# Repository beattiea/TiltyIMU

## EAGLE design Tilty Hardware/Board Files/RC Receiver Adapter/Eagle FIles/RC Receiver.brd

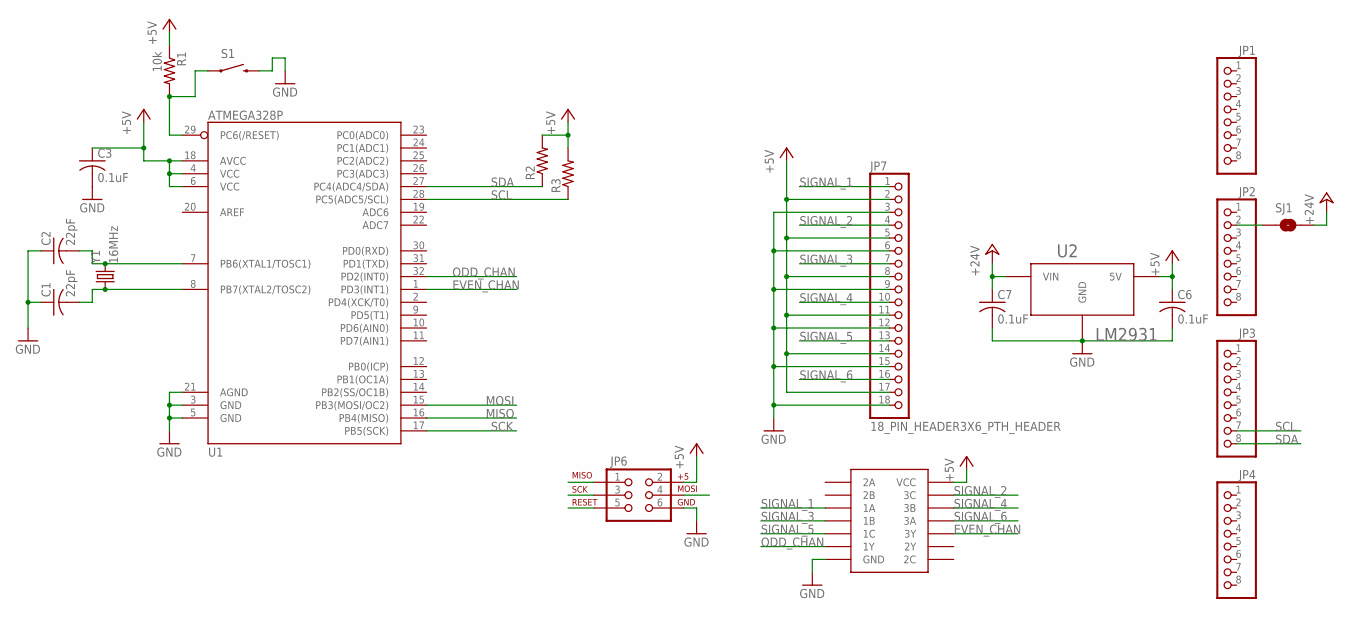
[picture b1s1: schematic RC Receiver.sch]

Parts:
C1, C2: 22pF; C0603
C3, C6, C7: 0.1uF; C0603
JP1, JP2, JP3, JP4: PINHD-1X81X08_NO_SILK; 1X08_NO_SS
JP6: AVR_SPI_PRG_62X3_LOCK; 2X3_LOCK
JP7: 18_PIN_HEADER3X6_PTH_HEADER; 3X6_PTH_HEADER
R1: 10k; R0603
R2, R3: R-US_R0603; R0603
S1: SWITCH-MOMENTARY-2SMD; TACTILE_SWITCH_SMD
SJ1: SOLDERJUMPERNC; SJ_2S
U1: ATMEGA328P; TQFP32-08
U2: LM2931; TO263; PART# lm2931
U$1: C74HC407514-SOIC; 14-SOIC; PART# 296-14534-1-ND
Y1: 16MHz; CRYSTAL-SMD-5X3; PART# 535-10226-1-ND

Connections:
+5V: C3.1, C6.1, JP6.2, JP7.2, JP7.5, JP7.8, JP7.11, JP7.14, JP7.17, R1.1, R2.2, R3.2, U1.4 (VCC), U1.6 (VCC), U1.18 (AVCC), U2.P$3 (5V), U$1.P$14 (VCC)
+24V: C7.1, SJ1.2, U2.P$2 (VIN)
EVEN_CHAN: U1.1 (PD3(INT1)), U$1.P$12 (3Y)
GND: C1.1, C2.1, C3.2, C6.2, C7.2, JP6.6, JP7.3, JP7.6, JP7.9, JP7.12, JP7.15, JP7.18, S1.3 (2), U1.3 (GND), U1.5 (GND), U1.21 (AGND), U2.P$1 (GND), U$1.P$13 (GND)
MISO: JP6.1, U1.16 (PB4(MISO))
MOSI: JP6.4, U1.15 (PB3(MOSI/OC2))
unnamed: C2.2, U1.7 (PB6(XTAL1/TOSC1)), Y1.3 (2)
unnamed: C1.2, U1.8 (PB7(XTAL2/TOSC2)), Y1.1
unnamed: JP2.2, SJ1.1
ODD_CHAN: U1.32 (PD2(INT0)), U$1.P$4 (1Y)
RESET: JP6.5, R1.2, S1.1, U1.29 (PC6(/RESET))
SCK: JP6.3, U1.17 (PB5(SCK))
SCL: JP3.7, R3.1, U1.28 (PC5(ADC5/SCL))
SDA: JP3.8, R2.1, U1.27 (PC4(ADC4/SDA))
SIGNAL_1: JP7.1, U$1.P$1 (1A)
SIGNAL_2: JP7.4, U$1.P$11 (3C)
SIGNAL_3: JP7.7, U$1.P$2 (1B)
SIGNAL_4: JP7.10, U$1.P$10 (3B)
SIGNAL_5: JP7.13, U$1.P$3 (1C)
SIGNAL_6: JP7.16, U$1.P$9 (3A)

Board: 2 copper layers, 20 parts (0 on the bottom side), 20 nets, no tracks yet.

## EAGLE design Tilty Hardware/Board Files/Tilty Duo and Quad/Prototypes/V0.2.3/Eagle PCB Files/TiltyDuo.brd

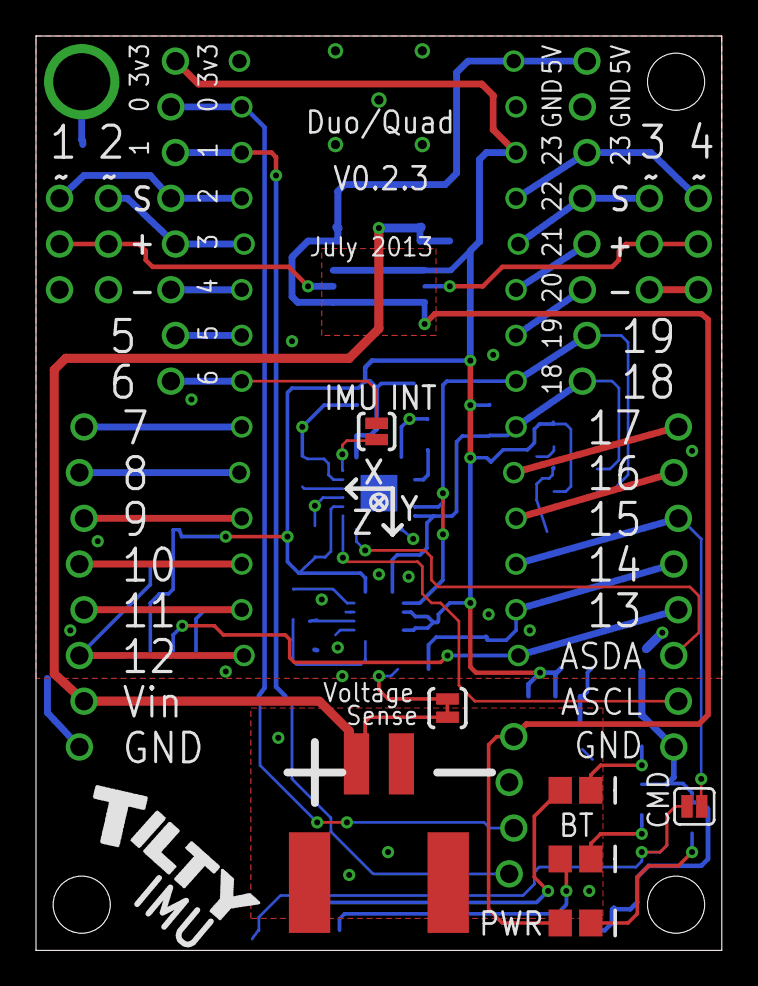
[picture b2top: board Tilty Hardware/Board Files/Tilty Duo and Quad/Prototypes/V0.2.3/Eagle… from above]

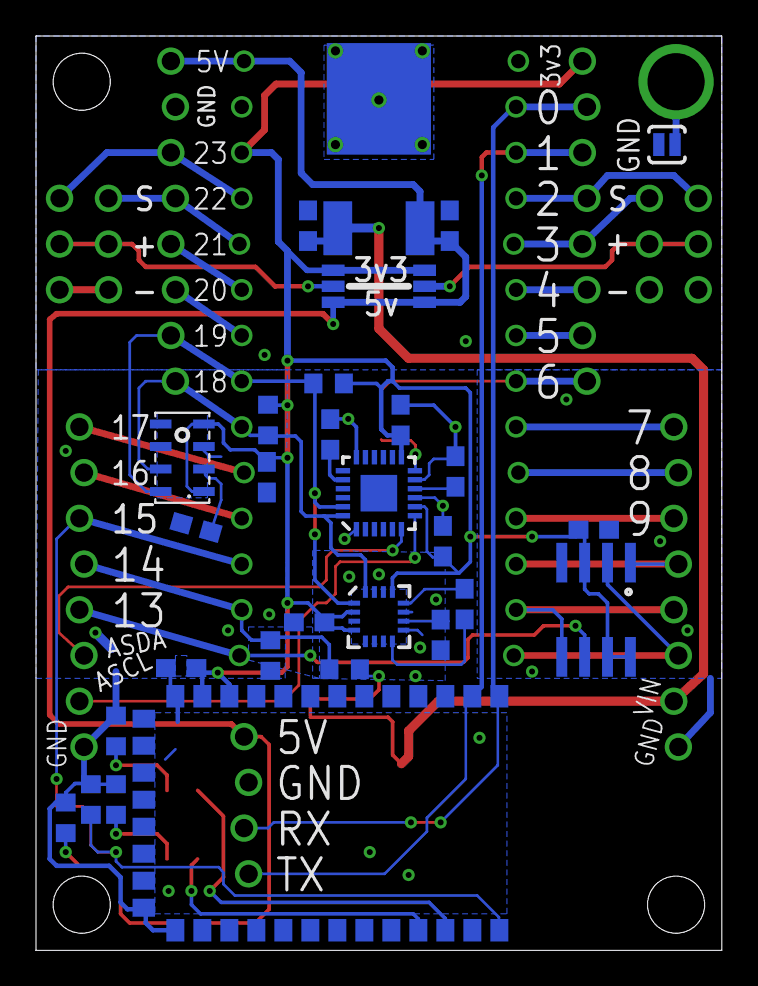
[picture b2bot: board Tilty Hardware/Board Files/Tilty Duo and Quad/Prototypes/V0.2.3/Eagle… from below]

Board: 2 copper layers, 38.1 x 50.8 mm, 45 parts (30 on the bottom side), 46 nets.

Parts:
C1, C2, C4, C5, C6, C9, C10, C11, C12, C13: 0.1uF; C0603
C3: 2.2nF; C0603
C7: 0.22uF; C0603
C8: 4.7uF; C0603
D1: RED; LED-0805
D2: GREEN; LED-0805
D3: YELLOW; LED-0805
JP1, JP2, JP5, JP6: 1X08_NO_SS_LOCKING
JP3, JP7: 2X03_NO_SS_LOCK
JP4: 2-POS_SMD_TERM_BLOCK; 2-POS_SMD_TERMINAL_BLOCK
JP9: 1X04_NO_SS_LOCKING
MPU_INT: SOLDERJUMPERNO; SJ_2S-NO
R1, R2: 4.7K; R0603
R3: 180; R0603
R4, R8: 68; R0603
R5: 10k; R0603
R6: 680; R0603
R7: 10K; R0603
SJ1: SOLDERJUMPERNO; SJ_2S-NO
SJ2, SJ3: SJ_3
SJ4: SOLDERJUMPERTRACE; SJ_2S-TRACE
SJ5: SJ_2S
U1: TEENSY_3.0_OUTER-PINS28-DIP_SOCKET; 28-DIP
U2: HC-09_BREAKOUT
U3: MPL3115A2LGA8; LGA8
U4: LM2931; TO263
U5: MPU-6050; QFN-24
U6: HMC5883LSMD; 16LPCC
U7: SPI_FLASH-X25XXSMD; SO08

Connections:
5V: C5.1, D2.1, JP5.8, JP9.4, SJ2.1, SJ3.1, U1.P$15, U4.P$3
AUXCL: JP6.2, U5.7
AUXDA: JP6.3, U5.6
BATT_SENSE: JP6.5, R5.2, R6.2, U1.P$27
BT_CMD: JP6.6, SJ5.1, U1.P$26
CMD: R7.2, SJ5.2, U2.P$34
CS: JP2.5, U1.P$12, U7.1
GND: C1.2, C2.1, C3.2, C4.2, C5.2, C6.2, C8.2, C9.2, C10.2, C11.1, C12.1, C13.1, JP2.1, JP3.1, JP3.2, JP4.P$4, JP5.7, JP6.1, JP7.1, JP7.2, JP9.3, R3.1, R4.2, R6.1, R7.1, R8.1, SJ1.2, U1.P$1, U1.P$16, U2.P$13, U2.P$21, U2.P$22, U3.3, U4.P$1, U5.1, U5.9, U5.11, U5.18, U6.9, U6.11, U7.4
I/O1: JP1.5, JP3.6, U1.P$4
I/O2: JP1.4, JP3.5, U1.P$5
I/O3: JP5.6, JP7.5, U1.P$18
I/O4: JP5.5, JP7.6, U1.P$19
MISO: JP2.3, U1.P$14, U7.2
MOSI: JP2.4, U1.P$13, U7.5
MPU_INT: JP1.1, MPU_INT.1, U1.P$8
unnamed: C1.1, U5.10
unnamed: C3.1, U5.20
unnamed: D1.2, R3.2
unnamed: C7.1, U6.8
unnamed: C7.2, U6.12
unnamed: JP1.3, U1.P$6
unnamed: JP1.2, U1.P$7
unnamed: R5.1, SJ4.2
unnamed: JP6.8, U1.P$24
unnamed: C8.1, U6.10
unnamed: JP2.6, U1.P$11
unnamed: D2.2, R4.1
unnamed: MPU_INT.2, U5.12
unnamed: JP5.4, U1.P$20
unnamed: JP5.3, U1.P$21
unnamed: C10.1, U3.2
unnamed: JP6.7, U1.P$25
unnamed: D3.2, R8.2
POW_I/O1: JP3.3, JP3.4, SJ2.2
POW_I/O2: JP7.3, JP7.4, SJ3.2
RED_LED: D1.1, U2.P$32
RX1: JP1.7, JP9.2, U1.P$2, U2.P$1
RX3: JP2.8, U1.P$9
SCK: JP6.4, U1.P$28, U7.6
SCL: JP5.2, R1.1, U1.P$22, U3.8, U5.23, U6.1
SDA: JP5.1, R2.1, U1.P$23, U3.7, U5.24, U6.16
TEENSY_3V3: C2.2, C6.1, C9.1, C11.2, C12.2, C13.2, JP1.8, R1.2, R2.2, SJ2.3, SJ3.3, U1.P$17, U2.P$11, U2.P$12, U3.1, U3.4, U5.8, U5.13, U6.2, U6.4, U6.13, U7.3, U7.7, U7.8
TX1: JP1.6, JP9.1, U1.P$3, U2.P$2
TX3: JP2.7, U1.P$10
VBATT: C4.1, JP2.2, JP4.P$3, SJ4.1, U4.P$2
YEL_LED: D3.1, U2.P$31

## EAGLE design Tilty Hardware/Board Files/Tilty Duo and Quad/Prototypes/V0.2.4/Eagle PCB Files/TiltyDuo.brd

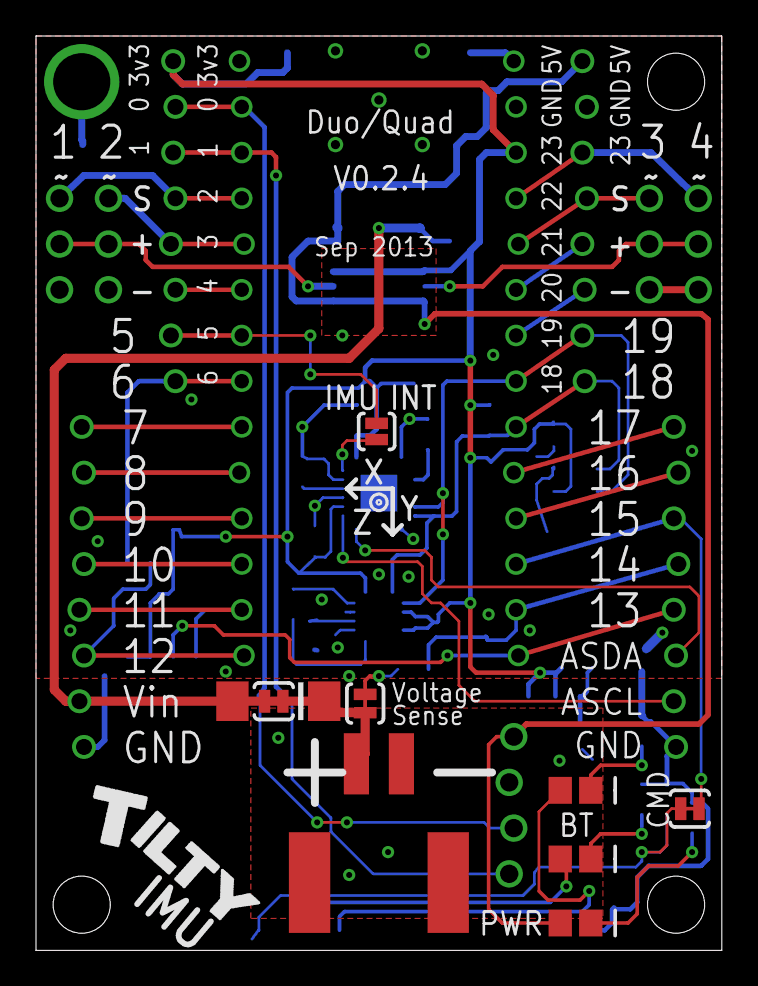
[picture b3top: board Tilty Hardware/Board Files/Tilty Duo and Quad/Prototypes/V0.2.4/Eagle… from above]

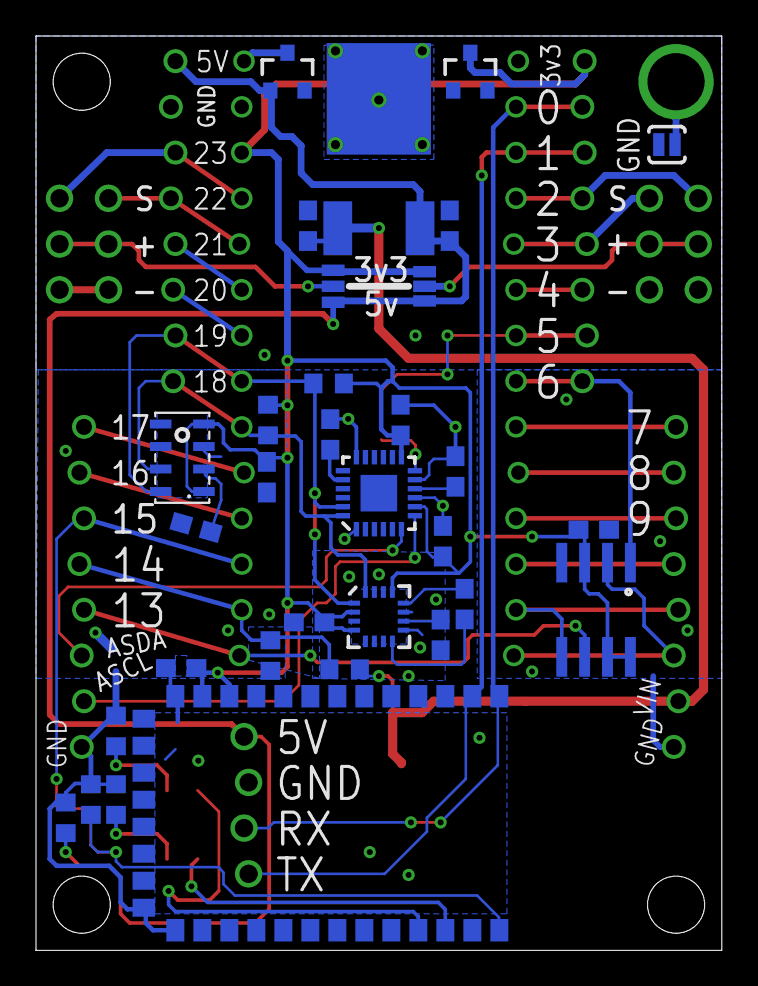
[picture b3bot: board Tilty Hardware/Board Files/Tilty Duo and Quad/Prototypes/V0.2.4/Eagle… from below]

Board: 2 copper layers, 38.1 x 50.8 mm, 49 parts (32 on the bottom side), 47 nets.

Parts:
C1, C2, C4, C6, C9, C10, C11, C12, C13: 0.1uF; C0603
C3: 2.2nF; C0603
C5, C8: 4.7uF; C0603
C7: 0.22uF; C0603
D1: RED; LED-0805
D2: GREEN; LED-0805
D3: YELLOW; LED-0805
D4, D5: SOT23-3
D6: DO214AA
JP1, JP2, JP3, JP4: 8-PIN_HEADER; 8-PIN_RECEPTACLE_LOCK_NO-SS
JP5: 2-POS_SMD_TERM_BLOCK; 2-POS_SMD_TERMINAL_BLOCK
JP6, JP7: 2X03_NO_SS_LOCK
JP9: 1X04_NO_SS_LOCKING
MPU_INT: SOLDERJUMPERNO; SJ_2S-NO
R1, R2: 4.7K; R0603
R3: 180; R0603
R4, R8: 68; R0603
R5: 10k; R0603
R6: 680; R0603
R7: 10K; R0603
SJ1: SOLDERJUMPERNO; SJ_2S-NO
SJ2: SJ_3_PASTE1&2
SJ3: SJ_3
SJ4, SJ5, SJ6: SOLDERJUMPERTRACE; SJ_2S-TRACE
U1: TEENSY_3.0_OUTER-PINS28-DIP_SOCKET; 28-DIP
U2: HC-09_BREAKOUT
U3: MPL3115A2LGA8; LGA8
U4: LM2931; TO263
U5: MPU-6050; QFN-24
U6: HMC5883LSMD; 16LPCC
U7: SPI_FLASH-X25XXSMD; SO08

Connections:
5V: C5.1, D2.1, D4.1, JP4.P$1, JP9.4, SJ2.1, SJ3.1, U4.P$3
AUXCL: JP3.P$7, U5.7
AUXDA: JP3.P$6, U5.6
BATT_SENSE: JP3.P$4, R5.2, R6.2, U1.P$27
BT_CMD: JP3.P$3, SJ5.1, U1.P$26
CMD: R7.2, SJ5.2, U2.P$34
CS: JP1.P$1, U1.P$8, U7.1
GND: C1.2, C2.1, C3.2, C4.2, C5.2, C6.2, C8.2, C9.2, C10.2, C11.1, C12.1, C13.1, D5.1, JP2.P$1, JP3.P$8, JP4.P$2, JP5.P$4, JP6.1, JP6.2, JP7.1, JP7.2, JP9.3, R3.1, R4.2, R6.1, R7.1, R8.1, SJ1.2, U1.P$1, U1.P$16, U2.P$13, U2.P$21, U2.P$22, U3.3, U4.P$1, U5.1, U5.9, U5.11, U5.18, U6.9, U6.11, U7.4
I/O1: JP1.P$5, JP6.6, U1.P$4
I/O2: JP1.P$4, JP6.5, U1.P$5
I/O3: JP4.P$3, JP7.5, U1.P$18
I/O4: JP4.P$4, JP7.6, U1.P$19
MISO: JP2.P$3, U1.P$14, U7.2
MOSI: JP2.P$4, U1.P$13, U7.5
MPU_INT: JP1.P$2, MPU_INT.1, U1.P$7
unnamed: C1.1, U5.10
unnamed: C3.1, U5.20
unnamed: D1.2, R3.2
unnamed: C7.1, U6.8
unnamed: C7.2, U6.12
unnamed: JP1.P$3, U1.P$6
unnamed: JP2.P$5, U1.P$12
unnamed: R5.1, SJ4.2
unnamed: JP3.P$1, U1.P$24
unnamed: C8.1, U6.10
unnamed: JP2.P$6, U1.P$11
unnamed: D2.2, R4.1
unnamed: D1.1, U2.P$31
unnamed: D4.3, U1.P$15
unnamed: MPU_INT.2, U5.12
unnamed: JP4.P$5, U1.P$20
unnamed: JP4.P$6, U1.P$21
unnamed: C10.1, U3.2
unnamed: JP3.P$2, U1.P$25
unnamed: D3.2, R8.2
POW_I/O1: JP6.3, JP6.4, SJ2.2
POW_I/O2: JP7.3, JP7.4, SJ3.2
RX1: JP1.P$7, JP9.2, U1.P$2, U2.P$1
RX3: JP2.P$8, U1.P$9
SCK: JP3.P$5, U1.P$28, U7.6
SCL: JP4.P$7, R1.1, U1.P$22, U3.8, U5.23, U6.1
SDA: JP4.P$8, R2.1, U1.P$23, U3.7, U5.24, U6.16
TEENSY_3V3: C2.2, C6.1, C9.1, C11.2, C12.2, C13.2, D5.3, JP1.P$8, R1.2, R2.2, SJ2.3, SJ3.3, U1.P$17, U2.P$11, U2.P$12, U3.1, U3.4, U5.8, U5.13, U6.2, U6.4, U6.13, U7.3, U7.7, U7.8
TX1: JP1.P$6, JP9.1, U1.P$3, U2.P$2
TX3: JP2.P$7, U1.P$10
VBATT: C4.1, D6.A, D6.C, JP2.P$2, JP5.P$3, SJ4.1, SJ6.1, SJ6.2, U4.P$2
YEL_LED: D3.1, U2.P$32

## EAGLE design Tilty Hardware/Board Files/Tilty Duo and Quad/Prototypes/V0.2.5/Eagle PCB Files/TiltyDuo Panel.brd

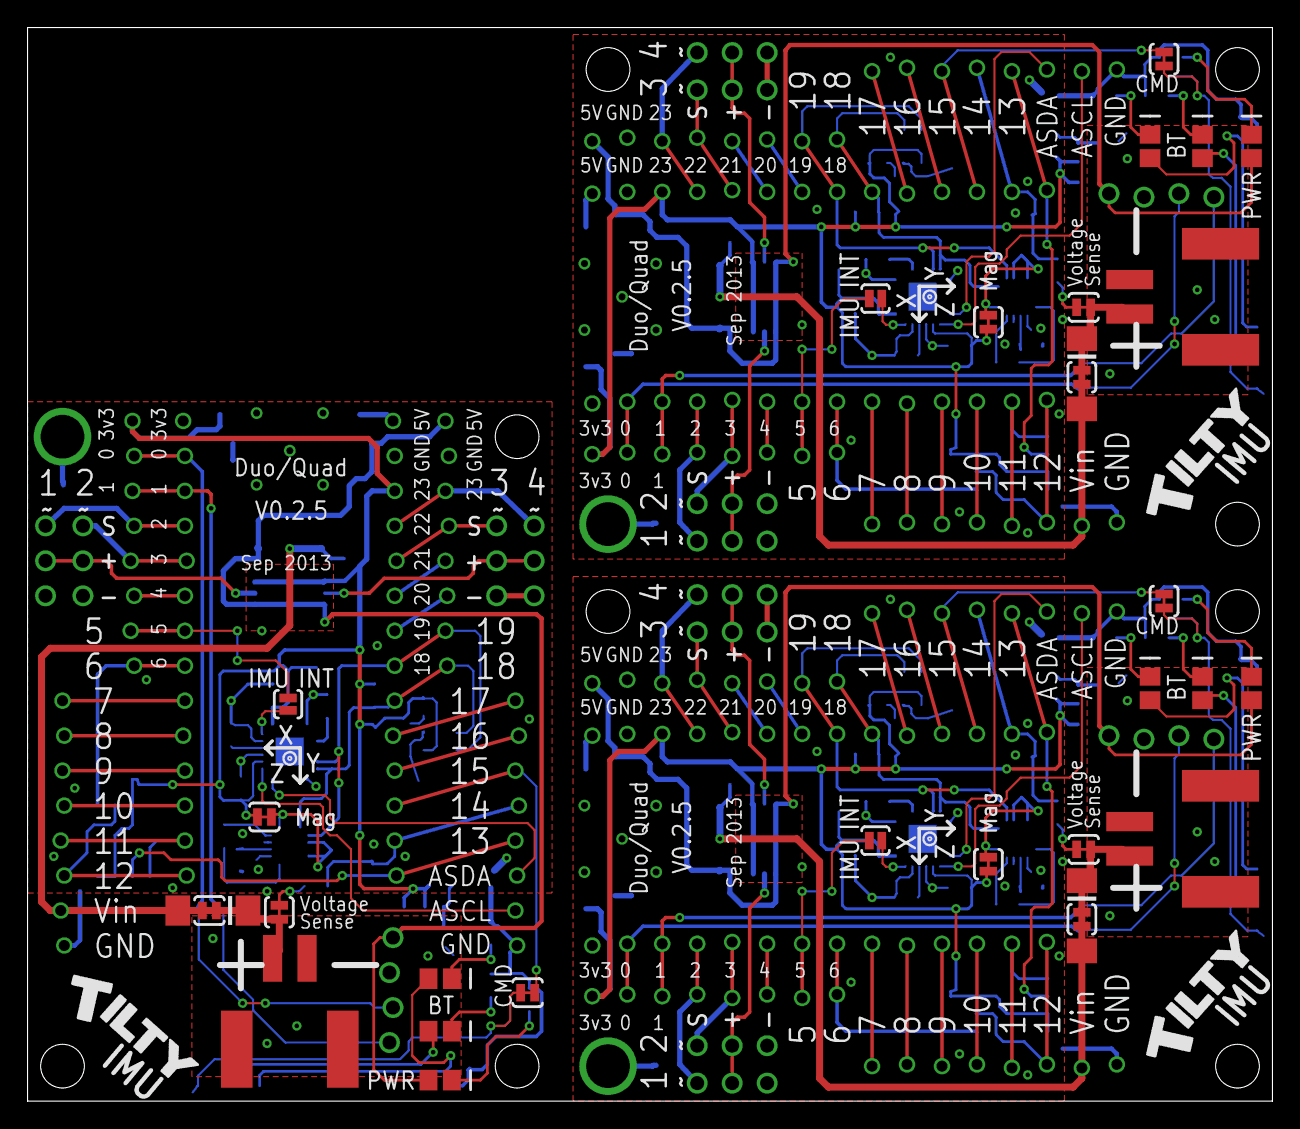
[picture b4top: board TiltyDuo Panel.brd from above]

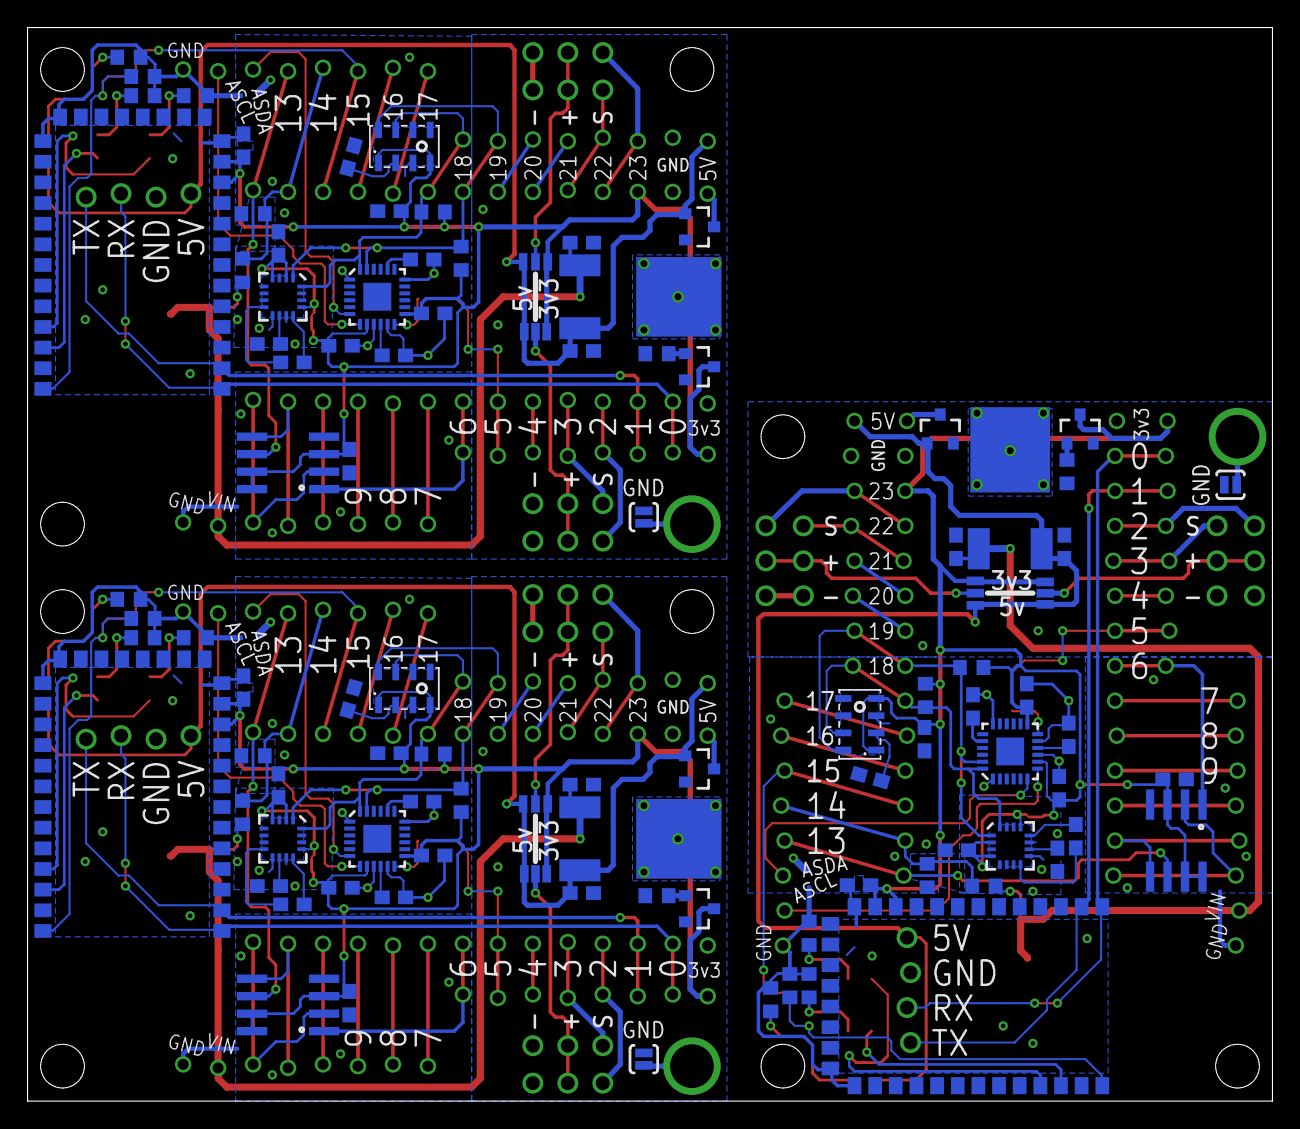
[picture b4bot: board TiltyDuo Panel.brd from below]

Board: 2 copper layers, 90.4 x 78.0 mm, 153 parts (99 on the bottom side), 147 nets.

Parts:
C1, C2, C4, C6, C9, C10, C11, C12, C13, C14, C15, C17, C21, C22, C23, C24, C25, C26, C27, C28, C30, C34, C35, C36, C37, C38, C39: 0.1uF; C0603
C3, C16, C29: 2.2nF; C0603
C5, C8, C18, C20, C31, C33: 4.7uF; C0603
C7, C19, C32: 0.22uF; C0603
D1, D7, D13: RED; LED-0805
D2, D8, D14: GREEN; LED-0805
D3, D9, D15: YELLOW; LED-0805
D4, D5, D10, D11, D16, D17: SOT23-3
D6, D12, D18: DO214AA
JP1, JP2, JP3, JP4, JP13, JP14, JP15, JP16, JP21, JP22, JP23, JP24: 8-PIN_HEADER; 8-PIN_RECEPTACLE_LOCK_NO-SS
JP5, JP8, JP17: 2-POS_SMD_TERM_BLOCK; 2-POS_SMD_TERMINAL_BLOCK
JP6, JP7, JP10, JP11, JP18, JP19: 2X03_NO_SS_LOCK
JP9, JP12, JP20: 1X04_NO_SS_LOCKING
MPU_INT, MPU_INT1, MPU_INT2: SOLDERJUMPERNO; SJ_2S-NO
R1, R2, R10, R11, R19, R20: 4.7K; R0603
R3, R15, R24: 180; R0603
R4, R8, R16, R17, R25, R26: 68; R0603
R5, R12, R21: 10k; R0603
R6, R13, R22: 680; R0603
R7, R14, R23: 10K; R0603
R9, R18, R27: R0603
SJ1, SJ8, SJ15: SOLDERJUMPERNO; SJ_2S-NO
SJ2, SJ10, SJ17: SJ_3_PASTE1&2
SJ3, SJ9, SJ16: SJ_3
SJ4, SJ5, SJ6, SJ7, SJ11, SJ12, SJ13, SJ14, SJ18, SJ19, SJ20, SJ21: SOLDERJUMPERTRACE; SJ_2S-TRACE
U1, U11, U18: TEENSY_3.0_OUTER-PINS28-DIP_SOCKET; 28-DIP
U2, U9, U16: HC-09_BREAKOUT
U3, U13, U20: MPL3115A2LGA8; LGA8
U4, U10, U17: LM2931; TO263
U5, U8, U15: MPU-6050; QFN-24
U6, U12, U19: HMC5883LSMD; 16LPCC
U7, U14, U21: SPI_FLASH-X25XXSMD; SO08

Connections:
5V: C5.1, D2.1, D4.1, JP4.P$1, JP9.4, SJ2.1, SJ3.1, U4.P$3
5V1: C18.1, D8.1, D10.1, JP12.4, JP13.P$1, SJ9.1, SJ10.1, U10.P$3
5V2: C31.1, D14.1, D16.1, JP20.4, JP21.P$1, SJ16.1, SJ17.1, U17.P$3
AUXCL: JP3.P$7, U5.7
AUXCL1: JP14.P$7, U8.7
AUXCL2: JP22.P$7, U15.7
AUXDA: JP3.P$6, U5.6
AUXDA1: JP14.P$6, U8.6
AUXDA2: JP22.P$6, U15.6
BATT_SENSE: JP3.P$4, R5.2, R6.2, U1.P$27
BATT_SENSE1: JP14.P$4, R12.2, R13.2, U11.P$27
BATT_SENSE2: JP22.P$4, R21.2, R22.2, U18.P$27
BT_CMD: JP3.P$3, SJ5.1, U1.P$26
BT_CMD1: JP14.P$3, SJ13.1, U11.P$26
BT_CMD2: JP22.P$3, SJ20.1, U18.P$26
CMD: R7.2, SJ5.2, U2.P$34
CMD1: R14.2, SJ13.2, U9.P$34
CMD2: R23.2, SJ20.2, U16.P$34
CS: JP1.P$1, U1.P$8, U7.1
CS1: JP16.P$1, U11.P$8, U14.1
CS2: JP24.P$1, U18.P$8, U21.1
GND: C1.2, C2.1, C3.2, C4.2, C5.2, C6.2, C8.2, C9.2, C10.2, C11.1, C12.1, C13.1, JP2.P$1, JP3.P$8, JP4.P$2, JP5.P$4, JP6.1, JP6.2, JP7.1, JP7.2, JP9.3, R3.1, R4.2, R6.1, R7.1, R8.1, R9.1, SJ1.2, U1.P$1, U1.P$16, U2.P$13, U2.P$21, U2.P$22, U3.3, U4.P$1, U5.1, U5.9, U5.11, U5.18, U6.9, U6.11, U7.4
GND1: C14.2, C15.1, C16.2, C17.2, C18.2, C20.2, C21.2, C22.2, C23.2, C24.1, C25.1, C26.1, JP8.P$4, JP10.1, JP10.2, JP11.1, JP11.2, JP12.3, JP13.P$2, JP14.P$8, JP15.P$1, R13.1, R14.1, R15.1, R16.1, R17.2, R18.1, SJ8.2, U8.1, U8.9, U8.11, U8.18, U9.P$13, U9.P$21, U9.P$22, U10.P$1, U11.P$1, U11.P$16, U12.9, U12.11, U13.3, U14.4
GND2: C27.2, C28.1, C29.2, C30.2, C31.2, C33.2, C34.2, C35.2, C36.2, C37.1, C38.1, C39.1, JP17.P$4, JP18.1, JP18.2, JP19.1, JP19.2, JP20.3, JP21.P$2, JP22.P$8, JP23.P$1, R22.1, R23.1, R24.1, R25.1, R26.2, R27.1, SJ15.2, U15.1, U15.9, U15.11, U15.18, U16.P$13, U16.P$21, U16.P$22, U17.P$1, U18.P$1, U18.P$16, U19.9, U19.11, U20.3, U21.4
I/O1: JP1.P$5, JP6.6, U1.P$4
I/O2: JP1.P$4, JP6.5, U1.P$5
I/O3: JP4.P$3, JP7.5, U1.P$18
I/O4: JP4.P$4, JP7.6, U1.P$19
I/O5: JP10.6, JP16.P$5, U11.P$4
I/O6: JP10.5, JP16.P$4, U11.P$5
I/O7: JP11.6, JP13.P$4, U11.P$19
I/O8: JP11.5, JP13.P$3, U11.P$18
I/O9: JP18.6, JP24.P$5, U18.P$4
I/O10: JP18.5, JP24.P$4, U18.P$5
I/O11: JP19.6, JP21.P$4, U18.P$19
I/O12: JP19.5, JP21.P$3, U18.P$18
MISO: JP2.P$3, U1.P$14, U7.2
MISO1: JP15.P$3, U11.P$14, U14.2
MISO2: JP23.P$3, U18.P$14, U21.2
MOSI: JP2.P$4, U1.P$13, U7.5
MOSI1: JP15.P$4, U11.P$13, U14.5
MOSI2: JP23.P$4, U18.P$13, U21.5
MPU_INT: JP1.P$2, MPU_INT.1, U1.P$7
MPU_INT1: JP16.P$2, MPU_INT1.1, U11.P$7
MPU_INT2: JP24.P$2, MPU_INT2.1, U18.P$7
unnamed: C1.1, U5.10
unnamed: C3.1, U5.20
unnamed: D1.2, R3.2
unnamed: C7.1, U6.8
unnamed: C7.2, U6.12
unnamed: JP1.P$3, U1.P$6
unnamed: JP2.P$5, U1.P$12
unnamed: R5.1, SJ4.2
unnamed: JP3.P$1, U1.P$24
unnamed: C8.1, U6.10
unnamed: JP2.P$6, U1.P$11
unnamed: D2.2, R4.1
unnamed: D1.1, U2.P$31
unnamed: D4.3, U1.P$15
unnamed: MPU_INT.2, U5.12
unnamed: C6.1, SJ7.2, U6.2, U6.4, U6.13
unnamed: JP4.P$5, U1.P$20
unnamed: JP4.P$6, U1.P$21
unnamed: C10.1, U3.2
unnamed: D5.1, R9.2
unnamed: JP3.P$2, U1.P$25
unnamed: D3.2, R8.2
unnamed: C14.1, U8.10
unnamed: C16.1, U8.20
unnamed: JP16.P$3, U11.P$6
unnamed: JP15.P$6, U11.P$11
unnamed: JP13.P$5, U11.P$20
unnamed: JP13.P$6, U11.P$21
unnamed: JP14.P$2, U11.P$25
unnamed: C19.1, U12.8
unnamed: C19.2, U12.12
unnamed: C20.1, U12.10
unnamed: MPU_INT1.2, U8.12
unnamed: C23.1, U13.2
unnamed: D7.2, R15.2
unnamed: D9.2, R16.2
unnamed: JP14.P$1, U11.P$24
unnamed: D8.2, R17.1
unnamed: R12.1, SJ11.2
unnamed: D7.1, U9.P$31
unnamed: JP15.P$5, U11.P$12
unnamed: D10.3, U11.P$15
unnamed: C21.1, SJ14.2, U12.2, U12.4, U12.13
unnamed: D11.1, R18.2
unnamed: C27.1, U15.10
unnamed: C29.1, U15.20
unnamed: JP24.P$3, U18.P$6
unnamed: JP23.P$6, U18.P$11
unnamed: JP21.P$5, U18.P$20
unnamed: JP21.P$6, U18.P$21
unnamed: JP22.P$2, U18.P$25
unnamed: C32.1, U19.8
unnamed: C32.2, U19.12
unnamed: C33.1, U19.10
unnamed: MPU_INT2.2, U15.12
unnamed: C36.1, U20.2
unnamed: D13.2, R24.2
unnamed: D15.2, R25.2
unnamed: JP22.P$1, U18.P$24
unnamed: D14.2, R26.1
unnamed: R21.1, SJ18.2
unnamed: D13.1, U16.P$31
unnamed: JP23.P$5, U18.P$12
unnamed: D16.3, U18.P$15
unnamed: C34.1, SJ21.2, U19.2, U19.4, U19.13
unnamed: D17.1, R27.2
POW_I/O1: JP6.3, JP6.4, SJ2.2
POW_I/O2: JP7.3, JP7.4, SJ3.2
POW_I/O3: JP11.3, JP11.4, SJ9.2
POW_I/O4: JP10.3, JP10.4, SJ10.2
POW_I/O5: JP19.3, JP19.4, SJ16.2
POW_I/O6: JP18.3, JP18.4, SJ17.2
RX1: JP1.P$7, JP9.2, U1.P$2, U2.P$1
RX2: JP15.P$8, U11.P$9
RX3: JP2.P$8, U1.P$9
RX4: JP12.2, JP16.P$7, U9.P$1, U11.P$2
RX5: JP23.P$8, U18.P$9
RX6: JP20.2, JP24.P$7, U16.P$1, U18.P$2
SCK: JP3.P$5, U1.P$28, U7.6
SCK1: JP14.P$5, U11.P$28, U14.6
SCK2: JP22.P$5, U18.P$28, U21.6
SCL: JP4.P$7, R1.1, U1.P$22, U3.8, U5.23, U6.1
SCL1: JP13.P$7, R10.1, U8.23, U11.P$22, U12.1, U13.8
SCL2: JP21.P$7, R19.1, U15.23, U18.P$22, U19.1, U20.8
SDA: JP4.P$8, R2.1, U1.P$23, U3.7, U5.24, U6.16
SDA1: JP13.P$8, R11.1, U8.24, U11.P$23, U12.16, U13.7
SDA2: JP21.P$8, R20.1, U15.24, U18.P$23, U19.16, U20.7
TEENSY_3V1: C15.2, C22.1, C24.2, C25.2, C26.2, D11.3, JP16.P$8, R10.2, R11.2, SJ9.3, SJ10.3, SJ14.1, U8.8, U8.13, U9.P$11, U9.P$12, U11.P$17, U13.1, U13.4, U14.3, U14.7, U14.8
TEENSY_3V2: C28.2, C35.1, C37.2, C38.2, C39.2, D17.3, JP24.P$8, R19.2, R20.2, SJ16.3, SJ17.3, SJ21.1, U15.8, U15.13, U16.P$11, U16.P$12, U18.P$17, U20.1, U20.4, U21.3, U21.7, U21.8
TEENSY_3V3: C2.2, C9.1, C11.2, C12.2, C13.2, D5.3, JP1.P$8, R1.2, R2.2, SJ2.3, SJ3.3, SJ7.1, U1.P$17, U2.P$11, U2.P$12, U3.1, U3.4, U5.8, U5.13, U7.3, U7.7, U7.8
TX1: JP1.P$6, JP9.1, U1.P$3, U2.P$2
TX2: JP15.P$7, U11.P$10
TX3: JP2.P$7, U1.P$10
TX4: JP12.1, JP16.P$6, U9.P$2, U11.P$3
TX5: JP23.P$7, U18.P$10
TX6: JP20.1, JP24.P$6, U16.P$2, U18.P$3
VBATT: C4.1, D6.A, D6.C, JP2.P$2, JP5.P$3, SJ4.1, SJ6.1, SJ6.2, U4.P$2
VBATT1: C17.1, D12.A, D12.C, JP8.P$3, JP15.P$2, SJ11.1, SJ12.1, SJ12.2, U10.P$2
VBATT2: C30.1, D18.A, D18.C, JP17.P$3, JP23.P$2, SJ18.1, SJ19.1, SJ19.2, U17.P$2
YEL_LED: D3.1, U2.P$32
YEL_LED1: D9.1, U9.P$32
YEL_LED2: D15.1, U16.P$32

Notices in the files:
parts and their libraries:
SparkFun-Passives: Licensing: CC v3.0 Share-Alike You are welcome to use this library for commercial purposes.
